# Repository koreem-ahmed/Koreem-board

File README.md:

# Koreem-board
this is my costumed keyboard with 2 OLED displays and RGP lights and a RP pico as a controller i made it with a 6.5 degrees slope to help in relaxing my hand when typing i made it becase i wanted a keyboard to help me programing and help me in typing. this was so cool journey to learn how ot program and how to make a keyboard from the scratch.

# the PCB

# the schamatic

# the 3d viewer

# The bottom part 

# the top part

# the whole pad

# the BOM
i searched on the parts on the internet and i found a varity of the quantaties and the prices so after researching the total cost for my keyboard is 155 USD dollars.

| Name                              | Amount | Price   | Source |
|-----------------------------------|--------|---------|--------|
| RP Pico 2040                      | 1      | $10     | [Most Electronics](https://mostelectronic.com/shop/arduino-development-boards/raspberry-pi/raspberry-pi-pico/) |
| Stabilizers for Cherry MX         | 1 set  | $15     | [Amazon Canada](https://www.amazon.ca/gp/product/B0725N5DG7/ref=ox_sc_act_image_1?smid=ANJIJSD0GGURT&psc=1) |
| Red Silent Linear Switches        | 110    | $50     | [Amazon Canada](https://www.amazon.ca/gp/product/B0DCPFBS57/ref=ox_sc_act_image_2?smid=A3DWYIK6Y9EEQB&psc=1) |
| 1N4148 Diode                      | 100    | $1.5    | [Ram Electronics](https://www.ram-e-shop.com/shop/1n4148-1n4148-high-speed-fast-switching-diode-300ma-100v-5636) |
| OLED Display (1.3")               | 2      | $7      | [Flux Electronics](https://fluxelectronix.com/shop/1-3-inch-oled-display-module-blue-128x64-4pin-i2c) |
| Keycaps                           | 1 set  | $8      | [Amazon Egypt](https://www.ram-e-shop.com/shop/rpi-pico-w-raspberry-pi-pico-w-wifi-8524) |
| WS2812B-V5/W LEDs                 | 100    | $6      | [LCSC](https://www.lcsc.com/product-detail/C2874885.html) |
| PCB from JLCPCB (no coupon)       | 1      | $33     | JLCPCB |
| **Total**                         | —      | **$130.5** | — |

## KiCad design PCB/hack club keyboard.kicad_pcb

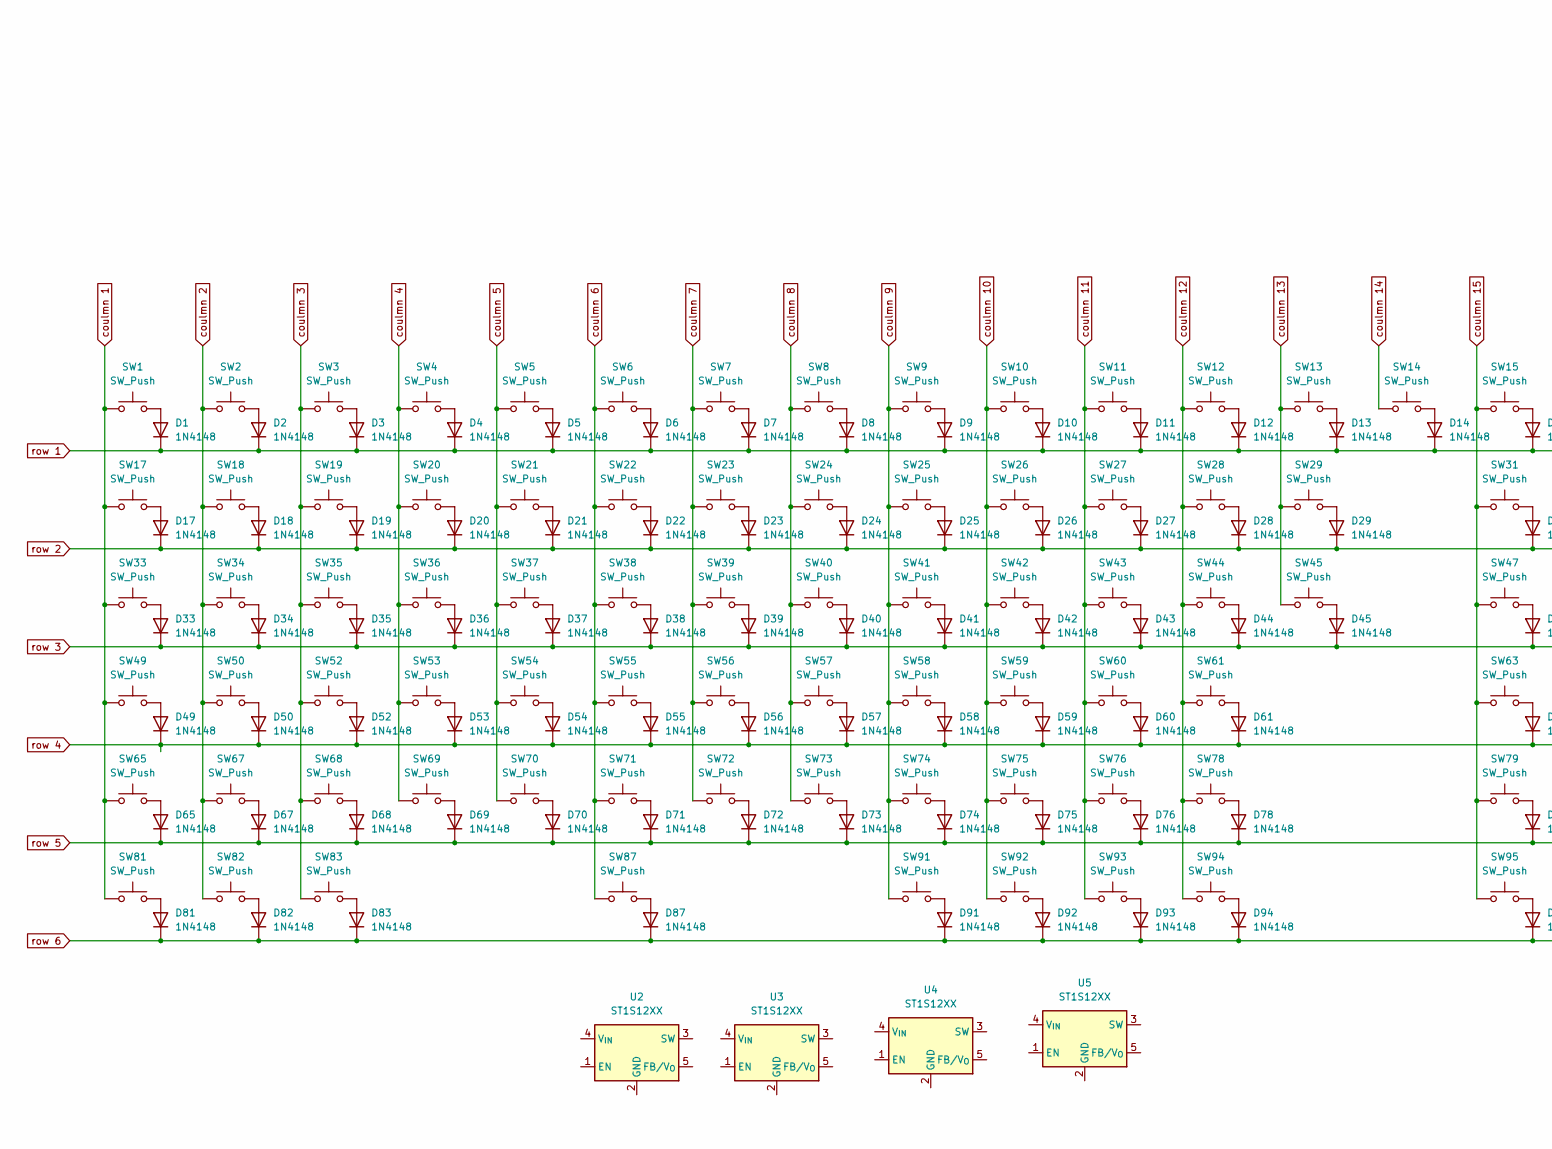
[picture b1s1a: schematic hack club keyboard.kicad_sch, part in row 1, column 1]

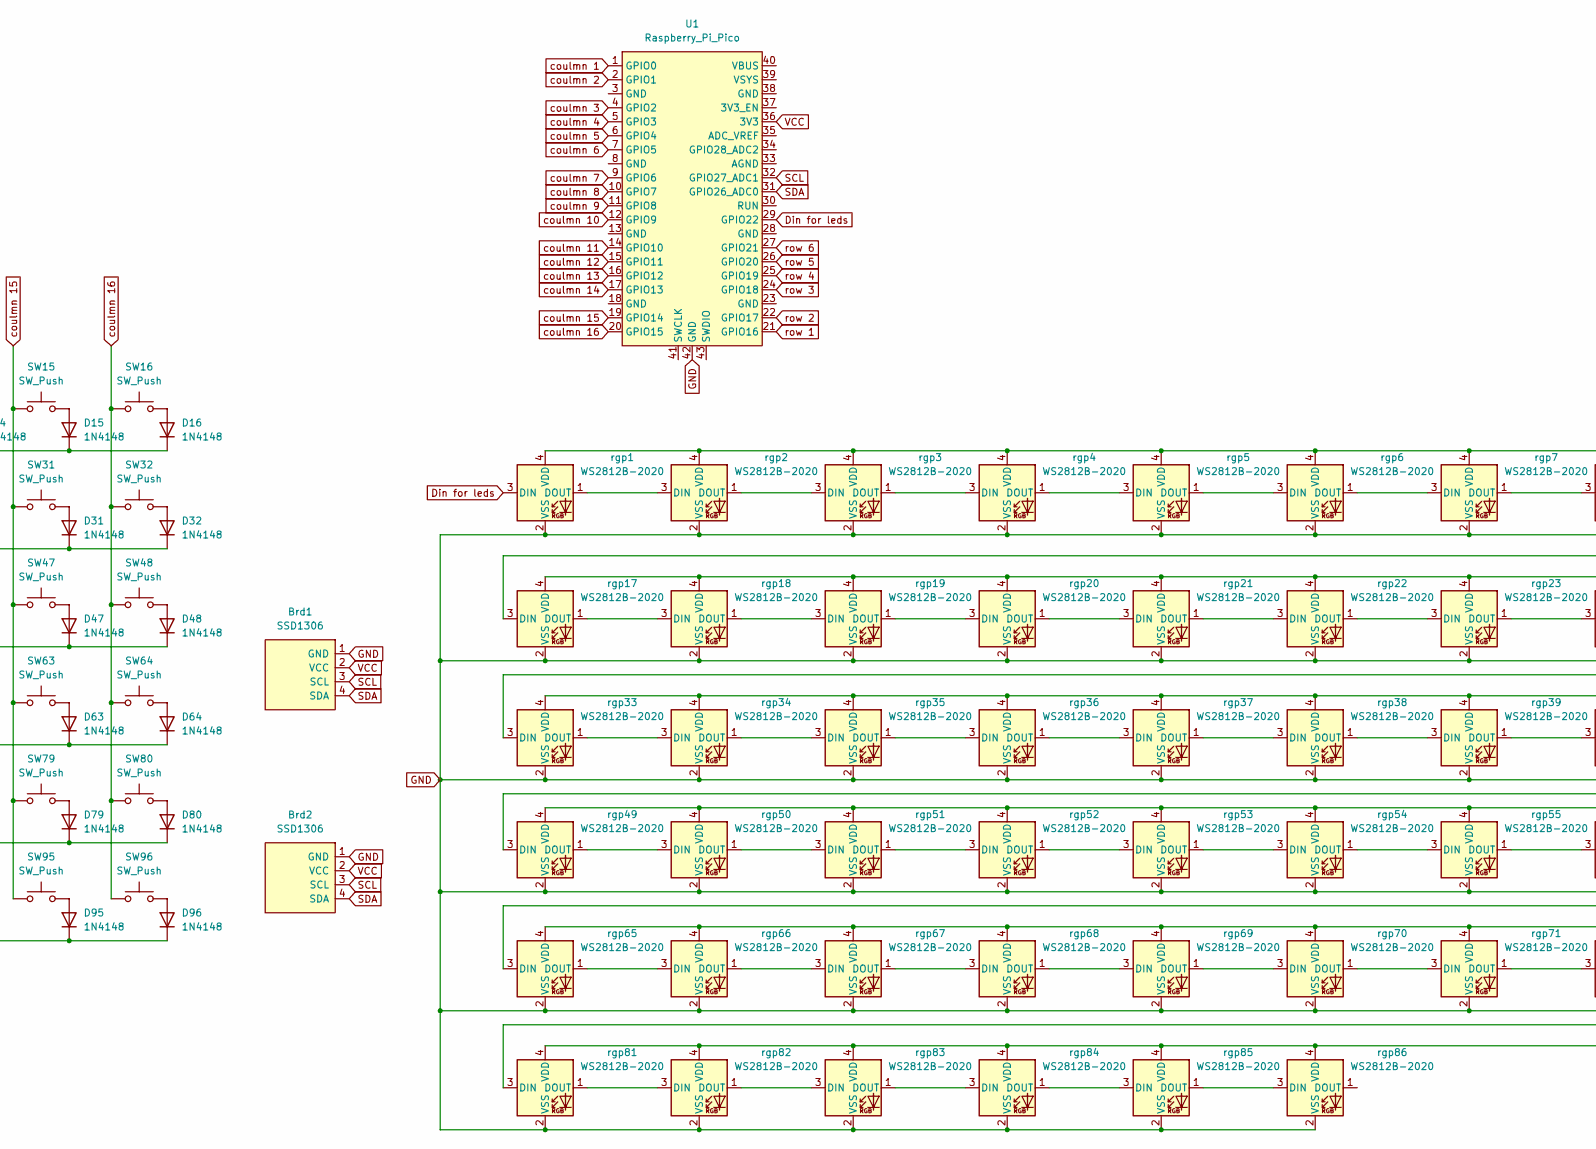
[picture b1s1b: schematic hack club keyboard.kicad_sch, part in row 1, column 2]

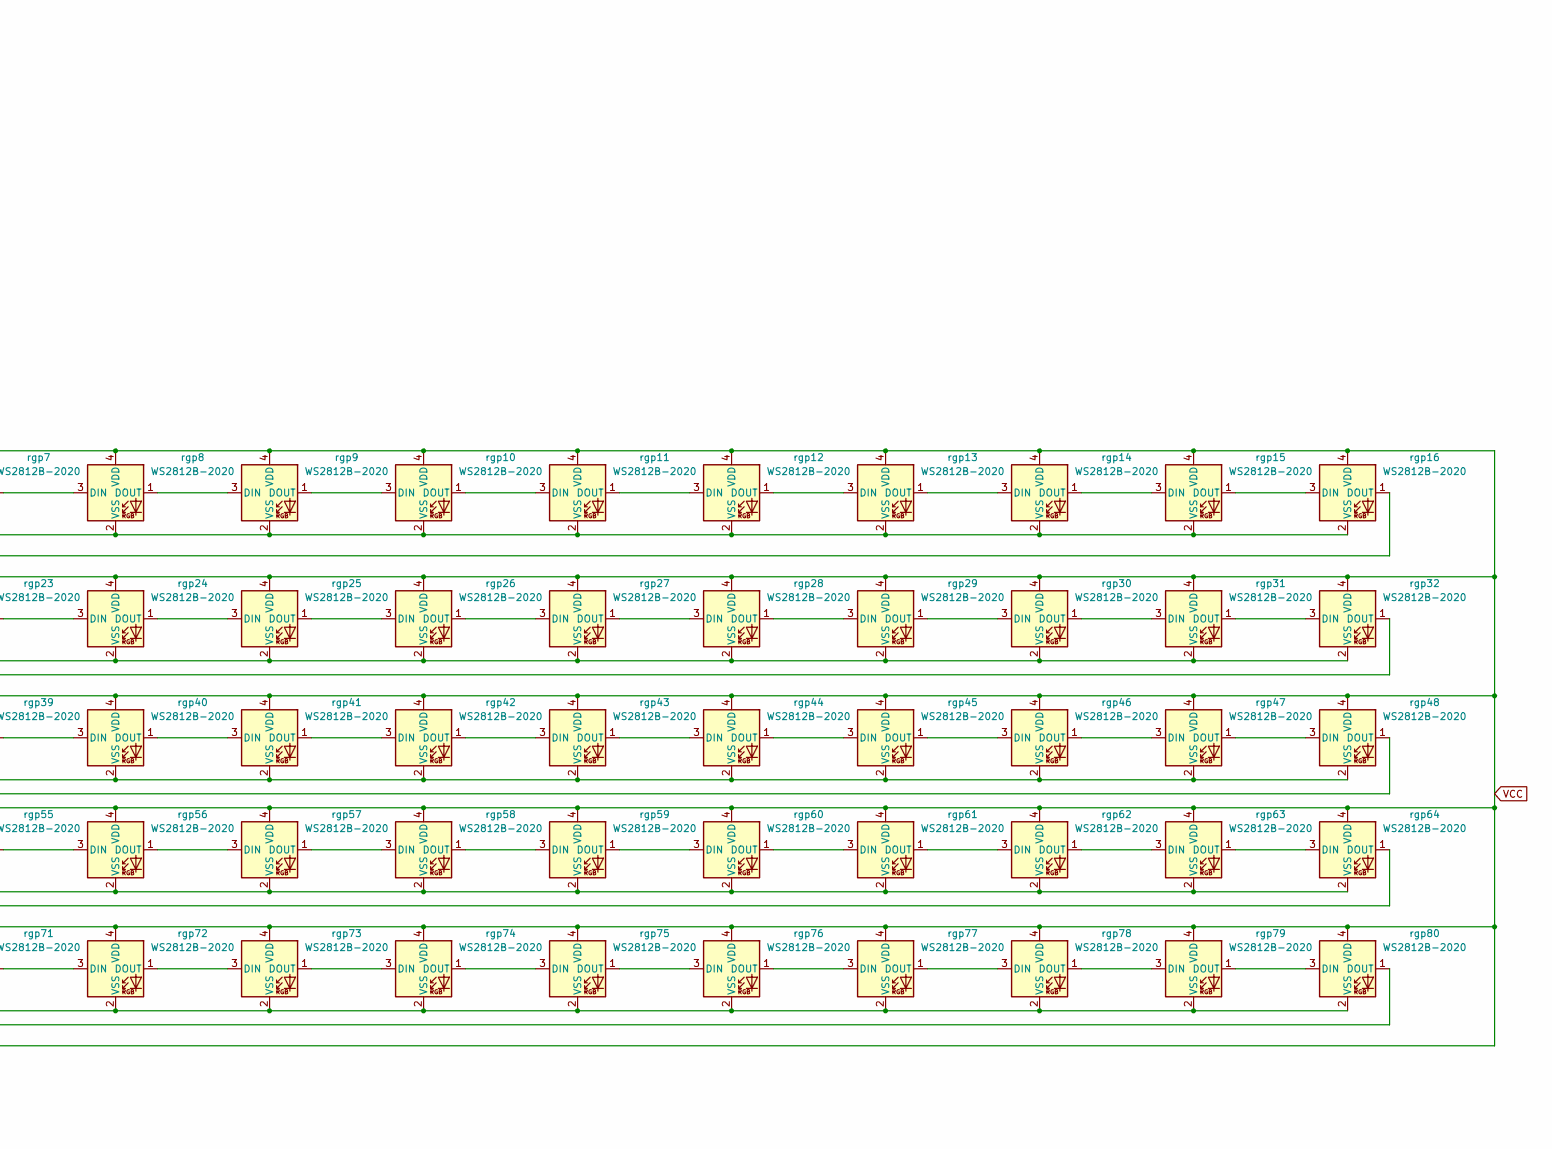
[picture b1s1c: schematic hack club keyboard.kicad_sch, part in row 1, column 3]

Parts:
Brd1, Brd2: SSD1306; OLED_128x64
D1, D2, D3, D4, D5, D6, D7, D8, D9, D10, D11, D12, D13, D14, D15, D16, D17, D18, D19, D20, D21, D22, D23, D24, D25, D26, D27, D28, D29, D31, D32, D33, D34, D35, D36, D37, D38, D39, D40, D41, D42, D43, D44, D45, D47, D48, D49, D50, D52, D53, D54, D55, D56, D57, D58, D59, D60, D61, D63, D64, D65, D67, D68, D69, D70, D71, D72, D73, D74, D75, D76, D78, D79, D80, D81, D82, D83, D87, D91, D92, D93, D94, D95, D96: 1N4148; D_DO-35_SOD27_P7.62mm_Horizontal
SW1, SW2, SW3, SW4, SW5, SW6, SW7, SW8, SW9, SW10, SW11, SW12, SW13, SW14, SW15, SW16, SW17, SW18, SW19, SW20, SW21, SW22, SW23, SW24, SW25, SW26, SW27, SW28, SW29, SW32, SW34, SW35, SW36, SW37, SW38, SW39, SW40, SW41, SW42, SW43, SW44, SW45, SW48, SW50, SW52, SW53, SW54, SW55, SW56, SW57, SW58, SW59, SW60, SW61, SW64, SW67, SW68, SW69, SW70, SW71, SW72, SW73, SW74, SW75, SW76, SW79, SW80, SW91, SW92, SW93, SW94, SW95, SW96: SW_Push; SW_Cherry_MX_1.00u_PCB koko
SW31: SW_Push; SW_Cherry_MX_2.00u_PCB
SW33, SW47: SW_Push; SW_Cherry_MX_1.50u_PCB
SW49, SW78: SW_Push; SW_Cherry_MX_1.75u_PCB
SW63, SW65: SW_Push; SW_Cherry_MX_2.25u_PCB
SW81, SW82, SW83: SW_Push; SW_Cherry_MX_1.25u_PCB
SW87: SW_Push; SW_Cherry_MX_6.25u_PCB
U1: Raspberry_Pi_Pico
U2, U3, U4: ST1S12XX; Stabilizer_Cherry_MX_2.00u
U5: ST1S12XX; Stabilizer_Cherry_MX_6.25u
rgp1, rgp2, rgp3, rgp4, rgp5, rgp6, rgp7, rgp8, rgp9, rgp10, rgp11, rgp12, rgp13, rgp14, rgp15, rgp16, rgp17, rgp18, rgp19, rgp20, rgp21, rgp22, rgp23, rgp24, rgp25, rgp26, rgp27, rgp28, rgp29, rgp30, rgp31, rgp32, rgp33, rgp34, rgp35, rgp36, rgp37, rgp38, rgp39, rgp40, rgp41, rgp42, rgp43, rgp44, rgp45, rgp46, rgp47, rgp48, rgp49, rgp50, rgp51, rgp52, rgp53, rgp54, rgp55, rgp56, rgp57, rgp58, rgp59, rgp60, rgp61, rgp62, rgp63, rgp64, rgp65, rgp66, rgp67, rgp68, rgp69, rgp70, rgp71, rgp72, rgp73, rgp74, rgp75, rgp76, rgp77, rgp78, rgp79, rgp80, rgp81, rgp82, rgp83, rgp84, rgp85, rgp86: WS2812B-2020; LED_WS2812B

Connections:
Din for leds: U1.29 (GPIO22), rgp1.3 (DIN)
GND: Brd1.1 (GND), Brd2.1 (GND), U1.42 (GND), rgp1.2 (VSS), rgp2.2 (VSS), rgp3.2 (VSS), rgp4.2 (VSS), rgp5.2 (VSS), rgp6.2 (VSS), rgp7.2 (VSS), rgp8.2 (VSS), rgp9.2 (VSS), rgp10.2 (VSS), rgp11.2 (VSS), rgp12.2 (VSS), rgp13.2 (VSS), rgp14.2 (VSS), rgp15.2 (VSS), rgp16.2 (VSS), rgp17.2 (VSS), rgp18.2 (VSS), rgp19.2 (VSS), rgp20.2 (VSS), rgp21.2 (VSS), rgp22.2 (VSS), rgp23.2 (VSS), rgp24.2 (VSS), rgp25.2 (VSS), rgp26.2 (VSS), rgp27.2 (VSS), rgp28.2 (VSS), rgp29.2 (VSS), rgp30.2 (VSS), rgp31.2 (VSS), rgp32.2 (VSS), rgp33.2 (VSS), rgp34.2 (VSS), rgp35.2 (VSS), rgp36.2 (VSS), rgp37.2 (VSS), rgp38.2 (VSS), rgp39.2 (VSS), rgp40.2 (VSS), rgp41.2 (VSS), rgp42.2 (VSS), rgp43.2 (VSS), rgp44.2 (VSS), rgp45.2 (VSS), rgp46.2 (VSS), rgp47.2 (VSS), rgp48.2 (VSS), rgp49.2 (VSS), rgp50.2 (VSS), rgp51.2 (VSS), rgp52.2 (VSS), rgp53.2 (VSS), rgp54.2 (VSS), rgp55.2 (VSS), rgp56.2 (VSS), rgp57.2 (VSS), rgp58.2 (VSS), rgp59.2 (VSS), rgp60.2 (VSS), rgp61.2 (VSS), rgp62.2 (VSS), rgp63.2 (VSS), rgp64.2 (VSS), rgp65.2 (VSS), rgp66.2 (VSS), rgp67.2 (VSS), rgp68.2 (VSS), rgp69.2 (VSS), rgp70.2 (VSS), rgp71.2 (VSS), rgp72.2 (VSS), rgp73.2 (VSS), rgp74.2 (VSS), rgp75.2 (VSS), rgp76.2 (VSS), rgp77.2 (VSS), rgp78.2 (VSS), rgp79.2 (VSS), rgp80.2 (VSS), rgp81.2 (VSS), rgp82.2 (VSS), rgp83.2 (VSS), rgp84.2 (VSS), rgp85.2 (VSS), rgp86.2 (VSS)
unnamed: D1.2 (A), SW1.2
unnamed: D2.2 (A), SW2.2
unnamed: D3.2 (A), SW3.2
unnamed: D4.2 (A), SW4.2
unnamed: D5.2 (A), SW5.2
unnamed: D6.2 (A), SW6.2
unnamed: D7.2 (A), SW7.2
unnamed: D8.2 (A), SW8.2
unnamed: D9.2 (A), SW9.2
unnamed: D10.2 (A), SW10.2
unnamed: D11.2 (A), SW11.2
unnamed: D12.2 (A), SW12.2
unnamed: D13.2 (A), SW13.2
unnamed: D14.2 (A), SW14.2
unnamed: D15.2 (A), SW15.2
unnamed: D16.2 (A), SW16.2
unnamed: D17.2 (A), SW17.2
unnamed: D18.2 (A), SW18.2
unnamed: D19.2 (A), SW19.2
unnamed: D20.2 (A), SW20.2
unnamed: D21.2 (A), SW21.2
unnamed: D22.2 (A), SW22.2
unnamed: D23.2 (A), SW23.2
unnamed: D24.2 (A), SW24.2
unnamed: D25.2 (A), SW25.2
unnamed: D26.2 (A), SW26.2
unnamed: D27.2 (A), SW27.2
unnamed: D28.2 (A), SW28.2
unnamed: D29.2 (A), SW29.2
unnamed: D31.2 (A), SW31.2
unnamed: D32.2 (A), SW32.2
unnamed: D33.2 (A), SW33.2
unnamed: D34.2 (A), SW34.2
unnamed: D35.2 (A), SW35.2
unnamed: D36.2 (A), SW36.2
unnamed: D37.2 (A), SW37.2
unnamed: D38.2 (A), SW38.2
unnamed: D39.2 (A), SW39.2
unnamed: D40.2 (A), SW40.2
unnamed: D41.2 (A), SW41.2
unnamed: D42.2 (A), SW42.2
unnamed: D43.2 (A), SW43.2
unnamed: D44.2 (A), SW44.2
unnamed: D45.2 (A), SW45.2
unnamed: D47.2 (A), SW47.2
unnamed: D48.2 (A), SW48.2
unnamed: D49.2 (A), SW49.2
unnamed: D50.2 (A), SW50.2
unnamed: D52.2 (A), SW52.2
unnamed: D53.2 (A), SW53.2
unnamed: D54.2 (A), SW54.2
unnamed: D55.2 (A), SW55.2
unnamed: D56.2 (A), SW56.2
unnamed: D57.2 (A), SW57.2
unnamed: D58.2 (A), SW58.2
unnamed: D59.2 (A), SW59.2
unnamed: D60.2 (A), SW60.2
unnamed: D61.2 (A), SW61.2
unnamed: D63.2 (A), SW63.2
unnamed: D64.2 (A), SW64.2
unnamed: D65.2 (A), SW65.2
unnamed: D67.2 (A), SW67.2
unnamed: D68.2 (A), SW68.2
unnamed: D69.2 (A), SW69.2
unnamed: D70.2 (A), SW70.2
unnamed: D71.2 (A), SW71.2
unnamed: D72.2 (A), SW72.2
unnamed: D73.2 (A), SW73.2
unnamed: D74.2 (A), SW74.2
unnamed: D75.2 (A), SW75.2
unnamed: D76.2 (A), SW76.2
unnamed: D78.2 (A), SW78.2
unnamed: D79.2 (A), SW79.2
unnamed: D80.2 (A), SW80.2
unnamed: D81.2 (A), SW81.2
unnamed: D82.2 (A), SW82.2
unnamed: D83.2 (A), SW83.2
unnamed: D87.2 (A), SW87.2
unnamed: D91.2 (A), SW91.2
unnamed: D92.2 (A), SW92.2
unnamed: D93.2 (A), SW93.2
unnamed: D94.2 (A), SW94.2
unnamed: D95.2 (A), SW95.2
unnamed: D96.2 (A), SW96.2
unnamed: rgp1.1 (DOUT), rgp2.3 (DIN)
unnamed: rgp2.1 (DOUT), rgp3.3 (DIN)
unnamed: rgp3.1 (DOUT), rgp4.3 (DIN)
unnamed: rgp4.1 (DOUT), rgp5.3 (DIN)
unnamed: rgp5.1 (DOUT), rgp6.3 (DIN)
unnamed: rgp6.1 (DOUT), rgp7.3 (DIN)
unnamed: rgp7.1 (DOUT), rgp8.3 (DIN)
unnamed: rgp8.1 (DOUT), rgp9.3 (DIN)
unnamed: rgp9.1 (DOUT), rgp10.3 (DIN)
unnamed: rgp10.1 (DOUT), rgp11.3 (DIN)
unnamed: rgp11.1 (DOUT), rgp12.3 (DIN)
unnamed: rgp12.1 (DOUT), rgp13.3 (DIN)
unnamed: rgp13.1 (DOUT), rgp14.3 (DIN)
unnamed: rgp14.1 (DOUT), rgp15.3 (DIN)
unnamed: rgp15.1 (DOUT), rgp16.3 (DIN)
unnamed: rgp16.1 (DOUT), rgp17.3 (DIN)
unnamed: rgp17.1 (DOUT), rgp18.3 (DIN)
unnamed: rgp18.1 (DOUT), rgp19.3 (DIN)
unnamed: rgp19.1 (DOUT), rgp20.3 (DIN)
unnamed: rgp20.1 (DOUT), rgp21.3 (DIN)
unnamed: rgp21.1 (DOUT), rgp22.3 (DIN)
unnamed: rgp22.1 (DOUT), rgp23.3 (DIN)
unnamed: rgp23.1 (DOUT), rgp24.3 (DIN)
unnamed: rgp24.1 (DOUT), rgp25.3 (DIN)
unnamed: rgp25.1 (DOUT), rgp26.3 (DIN)
unnamed: rgp26.1 (DOUT), rgp27.3 (DIN)
unnamed: rgp27.1 (DOUT), rgp28.3 (DIN)
unnamed: rgp28.1 (DOUT), rgp29.3 (DIN)
unnamed: rgp29.1 (DOUT), rgp30.3 (DIN)
unnamed: rgp30.1 (DOUT), rgp31.3 (DIN)
unnamed: rgp31.1 (DOUT), rgp32.3 (DIN)
unnamed: rgp32.1 (DOUT), rgp33.3 (DIN)
unnamed: rgp33.1 (DOUT), rgp34.3 (DIN)
unnamed: rgp34.1 (DOUT), rgp35.3 (DIN)
unnamed: rgp35.1 (DOUT), rgp36.3 (DIN)
unnamed: rgp36.1 (DOUT), rgp37.3 (DIN)
unnamed: rgp37.1 (DOUT), rgp38.3 (DIN)
unnamed: rgp38.1 (DOUT), rgp39.3 (DIN)
unnamed: rgp39.1 (DOUT), rgp40.3 (DIN)
unnamed: rgp40.1 (DOUT), rgp41.3 (DIN)
unnamed: rgp41.1 (DOUT), rgp42.3 (DIN)
unnamed: rgp42.1 (DOUT), rgp43.3 (DIN)
unnamed: rgp43.1 (DOUT), rgp44.3 (DIN)
unnamed: rgp44.1 (DOUT), rgp45.3 (DIN)
unnamed: rgp45.1 (DOUT), rgp46.3 (DIN)
unnamed: rgp46.1 (DOUT), rgp47.3 (DIN)
unnamed: rgp47.1 (DOUT), rgp48.3 (DIN)
unnamed: rgp48.1 (DOUT), rgp49.3 (DIN)
unnamed: rgp49.1 (DOUT), rgp50.3 (DIN)
unnamed: rgp50.1 (DOUT), rgp51.3 (DIN)
unnamed: rgp51.1 (DOUT), rgp52.3 (DIN)
unnamed: rgp52.1 (DOUT), rgp53.3 (DIN)
unnamed: rgp53.1 (DOUT), rgp54.3 (DIN)
unnamed: rgp54.1 (DOUT), rgp55.3 (DIN)
unnamed: rgp55.1 (DOUT), rgp56.3 (DIN)
unnamed: rgp56.1 (DOUT), rgp57.3 (DIN)
unnamed: rgp57.1 (DOUT), rgp58.3 (DIN)
unnamed: rgp58.1 (DOUT), rgp59.3 (DIN)
unnamed: rgp59.1 (DOUT), rgp60.3 (DIN)
unnamed: rgp60.1 (DOUT), rgp61.3 (DIN)
unnamed: rgp61.1 (DOUT), rgp62.3 (DIN)
unnamed: rgp62.1 (DOUT), rgp63.3 (DIN)
unnamed: rgp63.1 (DOUT), rgp64.3 (DIN)
unnamed: rgp64.1 (DOUT), rgp65.3 (DIN)
unnamed: rgp65.1 (DOUT), rgp66.3 (DIN)
unnamed: rgp66.1 (DOUT), rgp67.3 (DIN)
unnamed: rgp67.1 (DOUT), rgp68.3 (DIN)
unnamed: rgp68.1 (DOUT), rgp69.3 (DIN)
unnamed: rgp69.1 (DOUT), rgp70.3 (DIN)
unnamed: rgp70.1 (DOUT), rgp71.3 (DIN)
unnamed: rgp71.1 (DOUT), rgp72.3 (DIN)
unnamed: rgp72.1 (DOUT), rgp73.3 (DIN)
unnamed: rgp73.1 (DOUT), rgp74.3 (DIN)
unnamed: rgp74.1 (DOUT), rgp75.3 (DIN)
unnamed: rgp75.1 (DOUT), rgp76.3 (DIN)
unnamed: rgp76.1 (DOUT), rgp77.3 (DIN)
unnamed: rgp77.1 (DOUT), rgp78.3 (DIN)
unnamed: rgp78.1 (DOUT), rgp79.3 (DIN)
unnamed: rgp79.1 (DOUT), rgp80.3 (DIN)
unnamed: rgp80.1 (DOUT), rgp81.3 (DIN)
unnamed: rgp81.1 (DOUT), rgp82.3 (DIN)
unnamed: rgp82.1 (DOUT), rgp83.3 (DIN)
unnamed: rgp83.1 (DOUT), rgp84.3 (DIN)
unnamed: rgp84.1 (DOUT), rgp85.3 (DIN)
unnamed: rgp85.1 (DOUT), rgp86.3 (DIN)
SCL: Brd1.3 (SCL), Brd2.3 (SCL), U1.32 (GPIO27_ADC1)
SDA: Brd1.4 (SDA), Brd2.4 (SDA), U1.31 (GPIO26_ADC0)
VCC: Brd1.2 (VCC), Brd2.2 (VCC), U1.36 (3V3), rgp1.4 (VDD), rgp2.4 (VDD), rgp3.4 (VDD), rgp4.4 (VDD), rgp5.4 (VDD), rgp6.4 (VDD), rgp7.4 (VDD), rgp8.4 (VDD), rgp9.4 (VDD), rgp10.4 (VDD), rgp11.4 (VDD), rgp12.4 (VDD), rgp13.4 (VDD), rgp14.4 (VDD), rgp15.4 (VDD), rgp16.4 (VDD), rgp17.4 (VDD), rgp18.4 (VDD), rgp19.4 (VDD), rgp20.4 (VDD), rgp21.4 (VDD), rgp22.4 (VDD), rgp23.4 (VDD), rgp24.4 (VDD), rgp25.4 (VDD), rgp26.4 (VDD), rgp27.4 (VDD), rgp28.4 (VDD), rgp29.4 (VDD), rgp30.4 (VDD), rgp31.4 (VDD), rgp32.4 (VDD), rgp33.4 (VDD), rgp34.4 (VDD), rgp35.4 (VDD), rgp36.4 (VDD), rgp37.4 (VDD), rgp38.4 (VDD), rgp39.4 (VDD), rgp40.4 (VDD), rgp41.4 (VDD), rgp42.4 (VDD), rgp43.4 (VDD), rgp44.4 (VDD), rgp45.4 (VDD), rgp46.4 (VDD), rgp47.4 (VDD), rgp48.4 (VDD), rgp49.4 (VDD), rgp50.4 (VDD), rgp51.4 (VDD), rgp52.4 (VDD), rgp53.4 (VDD), rgp54.4 (VDD), rgp55.4 (VDD), rgp56.4 (VDD), rgp57.4 (VDD), rgp58.4 (VDD), rgp59.4 (VDD), rgp60.4 (VDD), rgp61.4 (VDD), rgp62.4 (VDD), rgp63.4 (VDD), rgp64.4 (VDD), rgp65.4 (VDD), rgp66.4 (VDD), rgp67.4 (VDD), rgp68.4 (VDD), rgp69.4 (VDD), rgp70.4 (VDD), rgp71.4 (VDD), rgp72.4 (VDD), rgp73.4 (VDD), rgp74.4 (VDD), rgp75.4 (VDD), rgp76.4 (VDD), rgp77.4 (VDD), rgp78.4 (VDD), rgp79.4 (VDD), rgp80.4 (VDD), rgp81.4 (VDD), rgp82.4 (VDD), rgp83.4 (VDD), rgp84.4 (VDD), rgp85.4 (VDD), rgp86.4 (VDD)
coulmn 1: SW1.1, SW17.1, SW33.1, SW49.1, SW65.1, SW81.1, U1.1 (GPIO0)
coulmn 2: SW2.1, SW18.1, SW34.1, SW50.1, SW67.1, SW82.1, U1.2 (GPIO1)
coulmn 3: SW3.1, SW19.1, SW35.1, SW52.1, SW68.1, SW83.1, U1.4 (GPIO2)
coulmn 4: SW4.1, SW20.1, SW36.1, SW53.1, SW69.1, U1.5 (GPIO3)
coulmn 5: SW5.1, SW21.1, SW37.1, SW54.1, SW70.1, U1.6 (GPIO4)
coulmn 6: SW6.1, SW22.1, SW38.1, SW55.1, SW71.1, SW87.1, U1.7 (GPIO5)
coulmn 7: SW7.1, SW23.1, SW39.1, SW56.1, SW72.1, U1.9 (GPIO6)
coulmn 8: SW8.1, SW24.1, SW40.1, SW57.1, SW73.1, U1.10 (GPIO7)
coulmn 9: SW9.1, SW25.1, SW41.1, SW58.1, SW74.1, SW91.1, U1.11 (GPIO8)
coulmn 10: SW10.1, SW26.1, SW42.1, SW59.1, SW75.1, SW92.1, U1.12 (GPIO9)
coulmn 11: SW11.1, SW27.1, SW43.1, SW60.1, SW76.1, SW93.1, U1.14 (GPIO10)
coulmn 12: SW12.1, SW28.1, SW44.1, SW61.1, SW78.1, SW94.1, U1.15 (GPIO11)
coulmn 13: SW13.1, SW29.1, SW45.1, U1.16 (GPIO12)
coulmn 14: SW14.1, U1.17 (GPIO13)
coulmn 15: SW15.1, SW31.1, SW47.1, SW63.1, SW79.1, SW95.1, U1.19 (GPIO14)
coulmn 16: SW16.1, SW32.1, SW48.1, SW64.1, SW80.1, SW96.1, U1.20 (GPIO15)
row 1: D1.1 (K), D2.1 (K), D3.1 (K), D4.1 (K), D5.1 (K), D6.1 (K), D7.1 (K), D8.1 (K), D9.1 (K), D10.1 (K), D11.1 (K), D12.1 (K), D13.1 (K), D14.1 (K), D15.1 (K), D16.1 (K), U1.21 (GPIO16)
row 2: D17.1 (K), D18.1 (K), D19.1 (K), D20.1 (K), D21.1 (K), D22.1 (K), D23.1 (K), D24.1 (K), D25.1 (K), D26.1 (K), D27.1 (K), D28.1 (K), D29.1 (K), D31.1 (K), D32.1 (K), U1.22 (GPIO17)
row 3: D33.1 (K), D34.1 (K), D35.1 (K), D36.1 (K), D37.1 (K), D38.1 (K), D39.1 (K), D40.1 (K), D41.1 (K), D42.1 (K), D43.1 (K), D44.1 (K), D45.1 (K), D47.1 (K), D48.1 (K), U1.24 (GPIO18)
row 4: D49.1 (K), D50.1 (K), D52.1 (K), D53.1 (K), D54.1 (K), D55.1 (K), D56.1 (K), D57.1 (K), D58.1 (K), D59.1 (K), D60.1 (K), D61.1 (K), D63.1 (K), D64.1 (K), U1.25 (GPIO19)
row 5: D65.1 (K), D67.1 (K), D68.1 (K), D69.1 (K), D70.1 (K), D71.1 (K), D72.1 (K), D73.1 (K), D74.1 (K), D75.1 (K), D76.1 (K), D78.1 (K), D79.1 (K), D80.1 (K), U1.26 (GPIO20)
row 6: D81.1 (K), D82.1 (K), D83.1 (K), D87.1 (K), D91.1 (K), D92.1 (K), D93.1 (K), D94.1 (K), D95.1 (K), D96.1 (K), U1.27 (GPIO21)

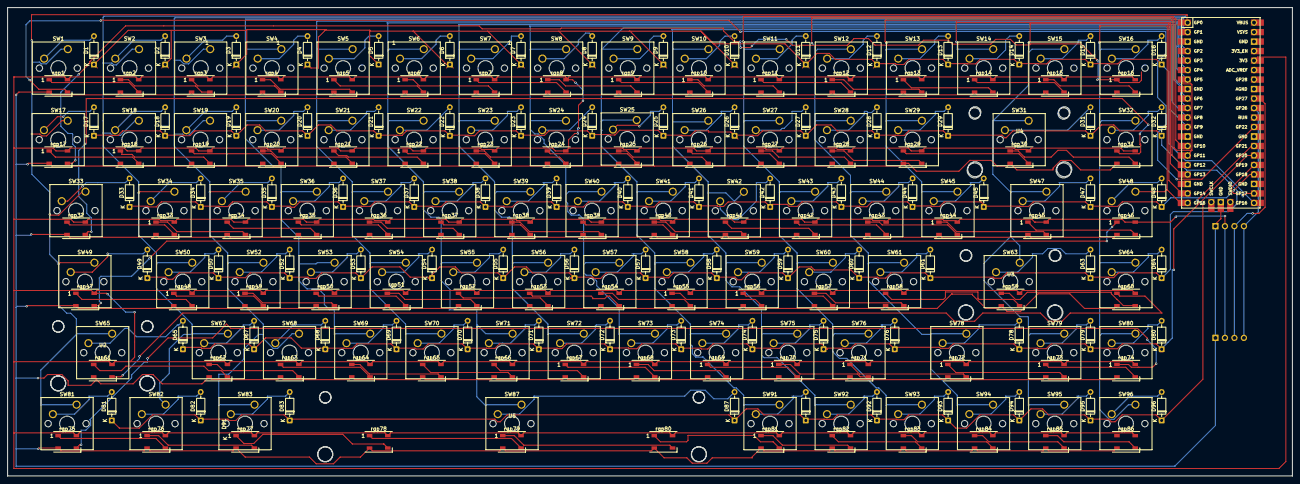
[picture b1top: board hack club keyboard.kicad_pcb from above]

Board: 2 copper layers, 343.9 x 125.3 mm, 261 parts (0 on the bottom side), 196 nets.

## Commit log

2025-07-26 Create BOM
2025-07-26 Update BOM
2025-08-02 Create Journal
2025-08-02 Rename BOM to BOM.csv
